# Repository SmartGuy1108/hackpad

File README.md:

# hackpad

My Hackpad is a 9 key macropad that uses 9 keyboard switches, a 0.96in oled screen, a xiao rp2040, 9 rgb leds, and a ATtiny85 for the leds. I made a PCB for this which can be found in the repo. It includes the gerber and drill files. My total price for this project was around $40 I used AliExpress to source the components for cheap and I used JLPCB for the PCB. The point of this was to make a maacropad that was cool and could be used for custom purposes instead of using the defualt layout. It works by making the Xiao do all the proccesing for the keys and the ATtiny doing all the led controls while being powered by the Xiao. I considered adding a usb C port for the ATtiny but decided against it to keep it all connected using one usb C so it looks clean. The total cost was around $48 I made a custom case that has a big hole for all the 9 keys because I didn't want they keycaps to get stuck on the lid. Here is the link to the OnShape project: https://cad.onshape.com/documents/e6c91fd51721781c7e785687/w/94b65f4af145f619cdb675ed/e/b2b440a0c79fd98d3f7bde3f?renderMode=0&uiState=6a04fa48d41efe3a6a1266aa. The lid connects to the body using "rails" in the body. I also added a hole on the top for the OLED. I added circles on each corner of the pcb groove to make sure it stayed in place. Here is a image of the case: 

Some Items I used were:

|#  |Component                                                |Quantity|Price   |Supplier  |Link                                                                                                                                                                                                                                                                                                                                                                                                                                                                                                                                                                                                                                                                    |
|---|---------------------------------------------------------|--------|--------|----------|------------------------------------------------------------------------------------------------------------------------------------------------------------------------------------------------------------------------------------------------------------------------------------------------------------------------------------------------------------------------------------------------------------------------------------------------------------------------------------------------------------------------------------------------------------------------------------------------------------------------------------------------------------------------|
|1  |XDA Profile PBT Blank Black Keycaps (MX compatible 10pcs)|10      |included|AliExpress|https://www.aliexpress.us/item/3256805328092200.html                                                                                                                                                                                                                                                                                                                                                                                                                                                                                                                                                                                                                    |
|2  |ATtiny85-20PU DIP-8 AVR Microcontroller                  |1       |included|AliExpress|https://www.aliexpress.us/item/3256808555620766.html?spm=a2g0o.productlist.main.11.801cl6gel6geQO&algo_pvid=50602609-ecce-48ad-855f-07c378396dc5&algo_exp_id=50602609-ecce-48ad-855f-07c378396dc5-10&pdp_ext_f=%7B%22order%22%3A%2221%22%2C%22eval%22%3A%221%22%2C%22fromPage%22%3A%22search%22%7D&pdp_npi=6%40dis%21USD%213.10%210.99%21%21%213.10%210.99%21%40210325a917783087227717348eeebc%2112000046478972951%21sea%21US%217621068922%21ABX%211%210%21n_tag%3A-29910%3Bd%3Af74fba6a%3Bm03_new_user%3A-29895%3BpisId%3A5000000203537318&curPageLogUid=gMP6Stg2v8xJ&utparam-url=scene%3Asearch%7Cquery_from%3A%7Cx_object_id%3A1005008741935518%7C_p_origin_prod%3A  |
|3  |SSD1306 0.96in 128x64 OLED Display (I2C white 3pcs)      |1       |included|AliExpress|https://www.aliexpress.us/item/3256805899077405.html                                                                                                                                                                                                                                                                                                                                                                                                                                                                                                                                                                                                                    |
|4  |WS2812B 5mm RGB Through-hole LED (5V diffused 10pcs)     |9       |included|AliExpress|https://www.aliexpress.us/item/3256806040849067.html?spm=a2g0o.productlist.main.10.7ab6paVEpaVEjr&algo_pvid=62cb0c92-1c9e-4fdd-96d2-34d27e3ec640&algo_exp_id=62cb0c92-1c9e-4fdd-96d2-34d27e3ec640-9&pdp_ext_f=%7B%22order%22%3A%221074%22%2C%22eval%22%3A%221%22%2C%22fromPage%22%3A%22search%22%7D&pdp_npi=6%40dis%21USD%218.65%210.99%21%21%2158.53%216.73%21%40210311c217783083894485439e7f81%2112000036369823577%21sea%21US%217621068922%21ABX%211%210%21n_tag%3A-29910%3Bd%3Af74fba6a%3Bm03_new_user%3A-29895%3BpisId%3A5000000203537318&curPageLogUid=7gXFasjcGqQz&utparam-url=scene%3Asearch%7Cquery_from%3A%7Cx_object_id%3A1005006227163819%7C_p_origin_prod%3A|
|5  |Outemu Blue 3-Pin MX Switches (10pcs)                    |10      |included|AliExpress|https://www.aliexpress.us/item/3256803795058460.html                                                                                                                                                                                                                                                                                                                                                                                                                                                                                                                                                                                                                    |
|6  |Custom PCB 2 layer black 5pcs (JLCPCB)                   |5       |$9.30   |JLCPCB    |N/A                                                                                                                                                                                                                                                                                                                                                                                                                                                                                                                                                                                                                                                                     |
|7  |AliExpress Subtotal                                      |-       |-       |$11.02    |-                                                                                                                                                                                                                                                                                                                                                                                                                                                                                                                                                                                                                                                                       |
|8  |AliExpress Total                                         |-       |-       |$11.02    |-                                                                                                                                                                                                                                                                                                                                                                                                                                                                                                                                                                                                                                                                       |
|9  |PCB + Shipping                                           |-       |-       |$12.00    |-                                                                                                                                                                                                                                                                                                                                                                                                                                                                                                                                                                                                                                                                       |
|10 |Grand Total                                              |-       |-       |$23.02    |-                                                                                                                                                                                                                                                                                                                                                                                                                                                                                                                                                                                                                                                                       |

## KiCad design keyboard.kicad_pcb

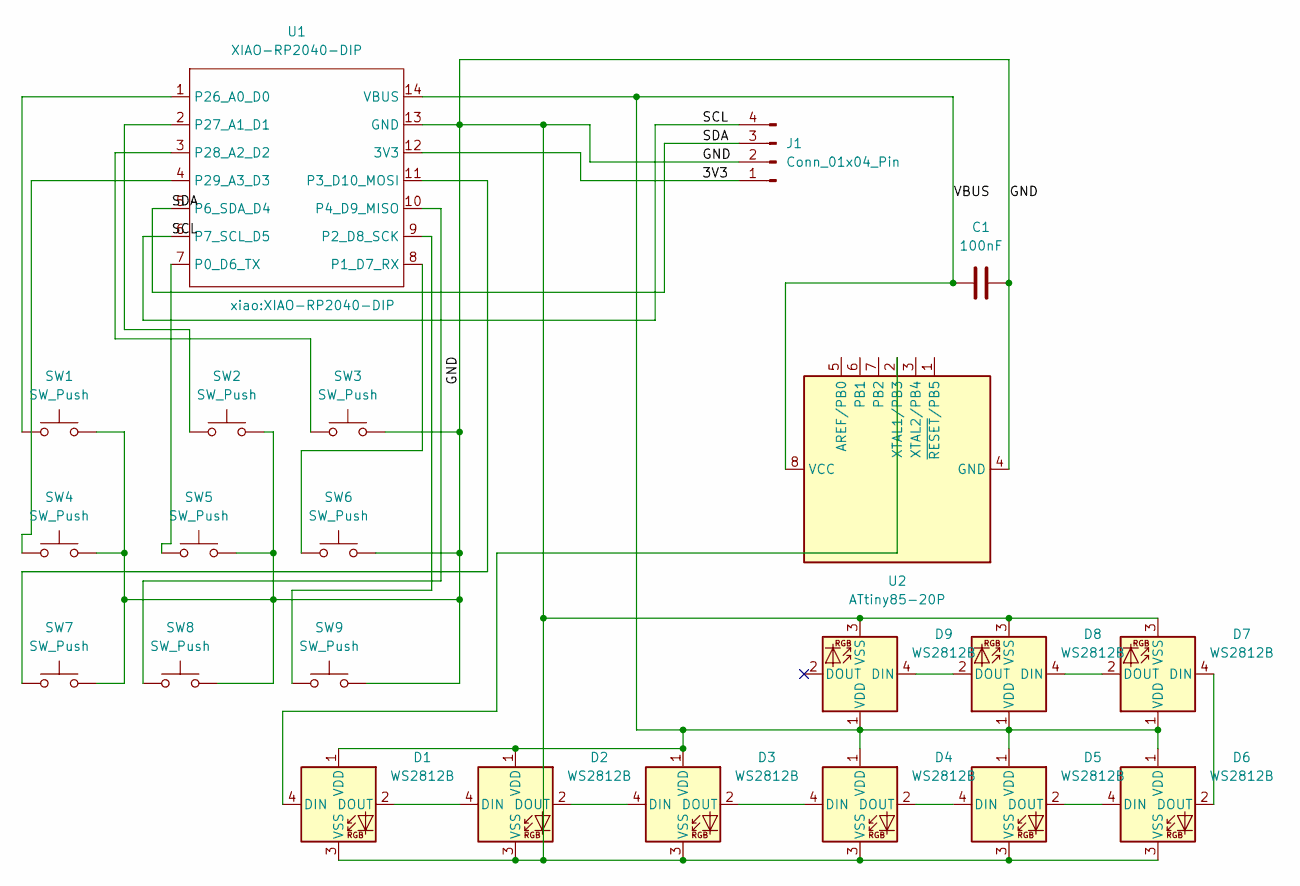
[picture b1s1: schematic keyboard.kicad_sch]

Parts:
C1: 100nF; C_Disc_D3.0mm_W2.0mm_P2.50mm
D1, D2, D3, D4, D5, D6, D7, D8, D9: WS2812B; LED_D5.0mm-4_RGB
J1: Conn_01x04_Pin; PinHeader_1x04_P2.54mm_Vertical
SW1, SW2, SW3, SW4, SW5, SW6, SW7, SW8, SW9: SW_Push; SW_Cherry_MX_1.00u_PCB
U1: XIAO-RP2040-DIP
U2: ATtiny85-20P; DIP-8_W7.62mm

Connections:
/3V3: J1.1, U1.12 (3V3)
/GND: C1.2, D1.3 (VSS), D2.3 (VSS), D3.3 (VSS), D4.3 (VSS), D5.3 (VSS), D6.3 (VSS), D7.3 (VSS), D8.3 (VSS), D9.3 (VSS), J1.2, SW1.2, SW2.2, SW3.2, SW4.2, SW5.2, SW6.2, SW7.2, SW8.2, SW9.2, U1.13 (GND), U2.4 (GND)
/SCL: J1.4, U1.6 (P7_SCL_D5)
/SDA: J1.3, U1.5 (P6_SDA_D4)
/VBUS: C1.1, D1.1 (VDD), D2.1 (VDD), D3.1 (VDD), D4.1 (VDD), D5.1 (VDD), D6.1 (VDD), D7.1 (VDD), D8.1 (VDD), D9.1 (VDD), U1.14 (VBUS), U2.8 (VCC)
unnamed: D1.4 (DIN), U2.2 (XTAL1/PB3)
unnamed: D1.2 (DOUT), D2.4 (DIN)
unnamed: D2.2 (DOUT), D3.4 (DIN)
unnamed: D3.2 (DOUT), D4.4 (DIN)
unnamed: D4.2 (DOUT), D5.4 (DIN)
unnamed: D5.2 (DOUT), D6.4 (DIN)
unnamed: D6.2 (DOUT), D7.4 (DIN)
unnamed: D7.2 (DOUT), D8.4 (DIN)
unnamed: D8.2 (DOUT), D9.4 (DIN)
unnamed: SW5.1, U1.7 (P0_D6_TX)
unnamed: SW6.1, U1.8 (P1_D7_RX)
unnamed: SW9.1, U1.9 (P2_D8_SCK)
unnamed: SW7.1, U1.11 (P3_D10_MOSI)
unnamed: SW8.1, U1.10 (P4_D9_MISO)
unnamed: SW1.1, U1.1 (P26_A0_D0)
unnamed: SW2.1, U1.2 (P27_A1_D1)
unnamed: SW3.1, U1.3 (P28_A2_D2)
unnamed: SW4.1, U1.4 (P29_A3_D3)

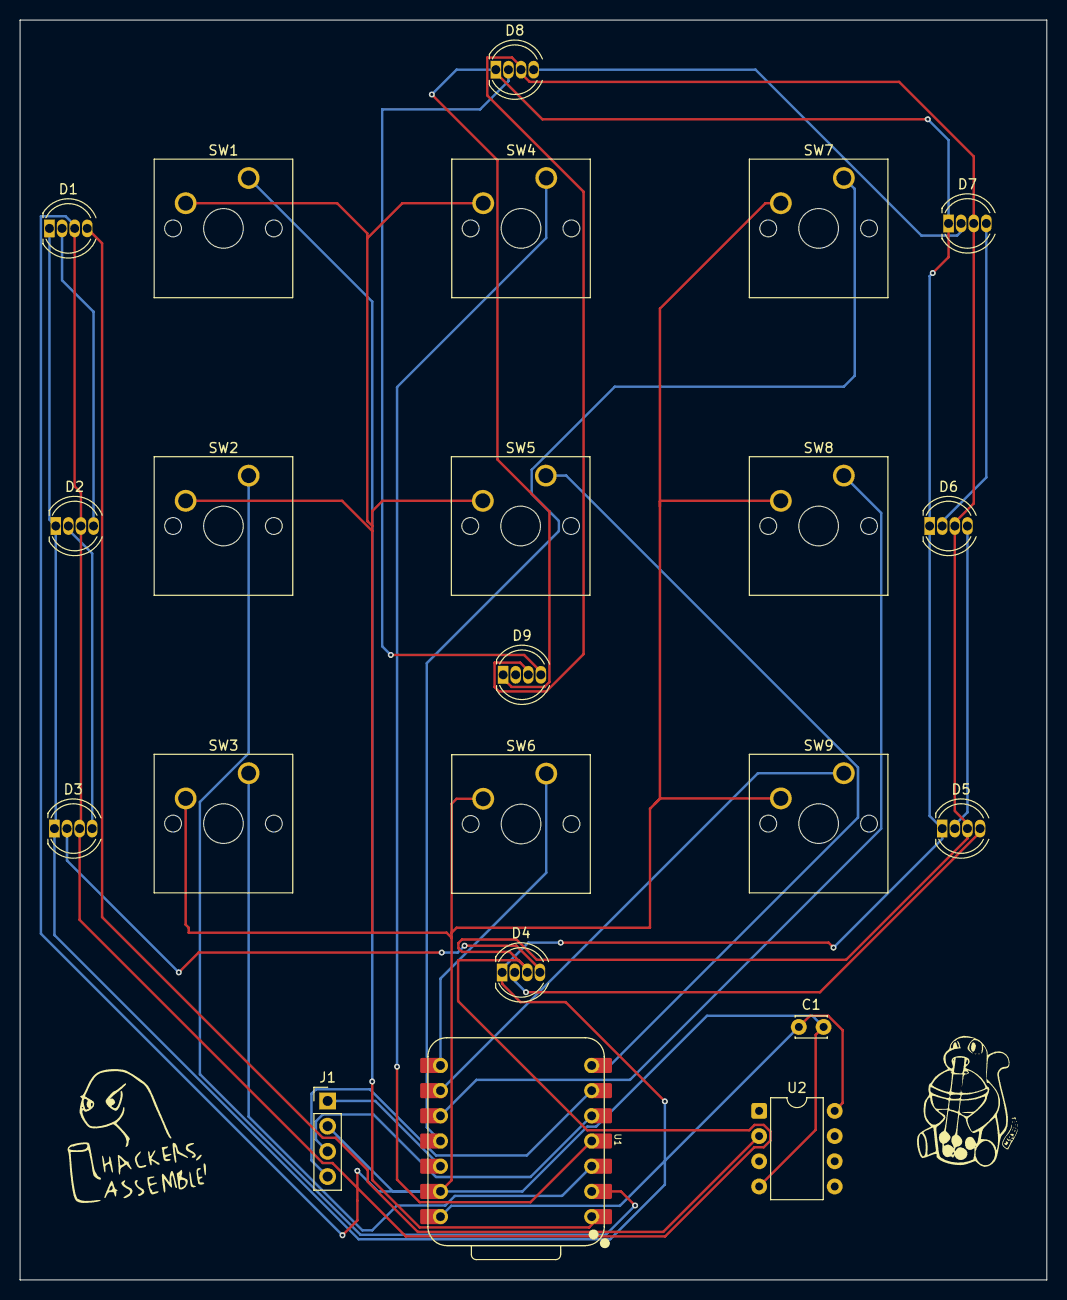
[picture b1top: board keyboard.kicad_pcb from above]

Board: 2 copper layers, 103.5 x 127.0 mm, 22 parts (0 on the bottom side), 23 nets.

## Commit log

2026-05-02 Add BOM for 9-Key Macropad with cost summary
    Added a Bill of Materials for a 9-Key Macropad, including components, quantities, prices, suppliers, and links.
2026-05-02 Fix formatting for WS2812B LEDs entry in bom.csv
2026-05-02 Clean up BOM by removing notes and header
    Removed unnecessary notes and header from BOM.
2026-05-02 Update README with project details and description
    Added project description and details about components and costs.
2026-05-02 Modify SSD1306 OLED Display description in bom.csv
    Updated the description of the SSD1306 OLED Display in the BOM.
2026-05-02 Convert BOM to CSV format with cost summary
    Updated the bill of materials to a CSV format with cost summary.
2026-05-02 Modify bom.csv to add placeholders for costs
    Updated cost entries in bom.csv to include placeholders for additional information.
2026-05-02 Remove unnecessary columns from bom.csv
2026-05-04 Add LED control for rainbow and breathing effects
2026-05-04 Add initial implementation of macro pad functionality
2026-05-04 Rename keyboard-for-production.zip to PCB/keyboard-for-production.zip
2026-05-04 Rename Keyboard.zip to PCB/Keyboard.zip
2026-05-04 Rename Macropad-case.step to Case/Macropad-case.step
2026-05-04 Enhance README with custom case details
    Expanded description of the Hackpad project, detailing the custom case design and features.
2026-05-04 Add image of the Hackpad case to README
    Updated the README to include an image of the case.
2026-05-04 Rename Screenshot 2026-05-03 123921.png to Screenshots/Screenshot 2026-05-03 123921.png
2026-05-04 Rename JLPCB.zip to PCB/JLPCB.zip
2026-05-04 Change PCB shipping cost to $12.00
    Updated PCB fabrication and shipping cost in BOM.
2026-05-05 Include images of the macropad case in README
    Added images of the custom case for the macropad.
2026-05-05 Revise Hackpad description and details
    Updated project description to include processing details and cost.
2026-05-05 Update README with new image of custom case
    Added an additional image of the custom case for the macropad.
2026-05-05 Update README with new project case images
    Added an additional image of the project case to the README.
2026-05-06 Remove duplicate content in README.md
    Removed duplicate description of the Hackpad project and retained the original content.
2026-05-07 Update README with additional case image
    Added an image of the custom case for the macropad.
2026-05-07 Add new image to README
    Added an additional image to the README.
2026-05-07 Rename keyboard-together-(3mf).3mf to FINAL-MODEL/keyboard-together-(3mf).3mf
2026-05-07 Rename keyboard-together.stl to FINAL-MODEL/keyboard-together.stl
2026-05-09 Update bom.csv by removing duplicates and adjusting totals
    Removed duplicate entries and updated totals.
2026-05-09 Adjust AliExpress subtotal in bom.csv
    Updated AliExpress subtotal to reflect new total.
2026-05-09 Fix link for WS2812B RGB LED in bom.csv
    Updated the link for WS2812B LED in the BOM.
2026-05-09 Change price of Custom PCB in bom.csv
    Updated the price of Custom PCB from $5.00 to $9.30.
2026-05-09 Update component links and pricing in bom.csv
    Updated the AliExpress link for the ATtiny85-20PU and adjusted the subtotal and grand total values.
2026-05-10 Add component list to README
    Added a table listing components, quantities, prices, suppliers, and links for reference.
2026-05-10 Remove component list from README
    Removed the component list from the README.
2026-05-14 Add component list to README
    Added a table listing components with their quantities, prices, suppliers, and links.
2026-05-14 Update README to summarize used components
    Removed the detailed components list and added a summary of items used.
2026-05-14 Add additional items to the README
2026-05-17 Rename keyboard-case (1).stl to keyboard-case.stl
2026-05-17 Update images in README and add new item list
    Replaced an image in the README and added a new image.
2026-05-18 Rename keyboard.stl to case-with-honeycombs.stl
2026-05-18 Fix typos and update images in README
    Updated images and corrected typos in the README.
2026-05-18 Update images in README.md
    Replaced an image in the README and added a new image.
2026-05-19 Add new images to README
    Added two new images to the README.
2026-05-24 Refactor component list into a markdown table
    Formatted the component list into a table for better readability and added additional components with their details.
2026-05-29 Update image in README.md
    Replaced an image in the README with a new one.
